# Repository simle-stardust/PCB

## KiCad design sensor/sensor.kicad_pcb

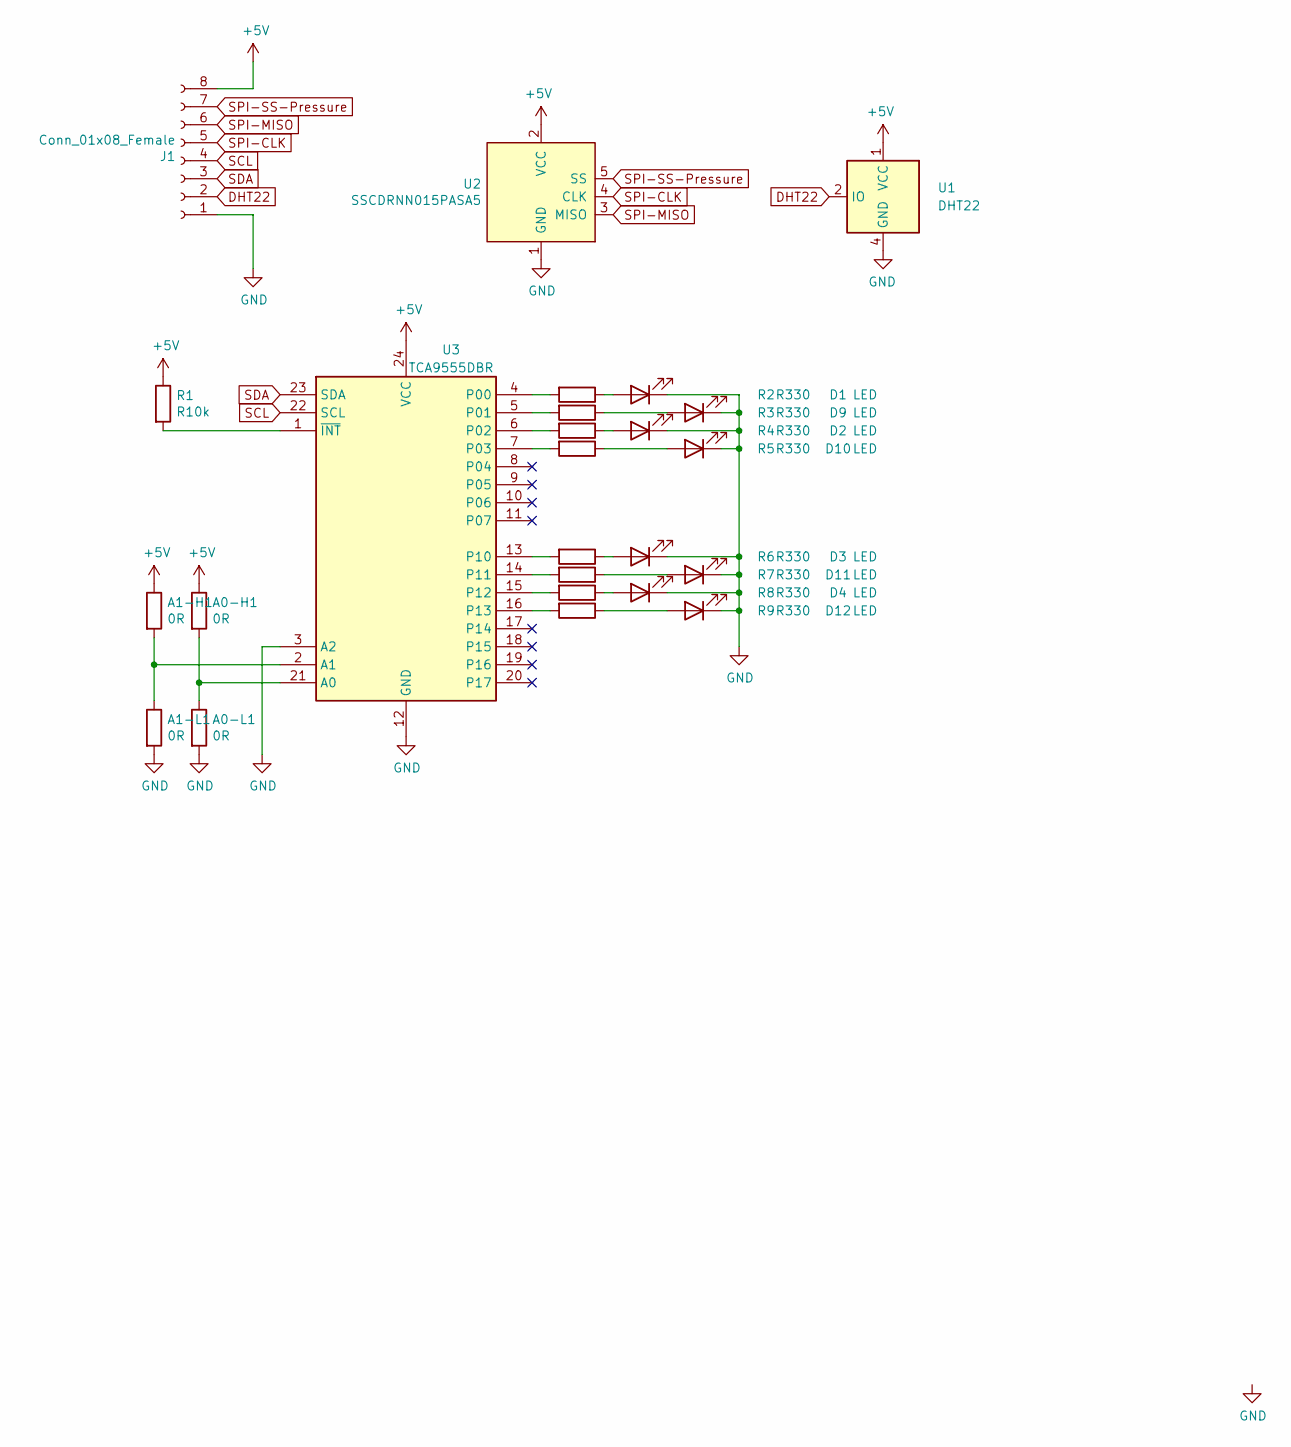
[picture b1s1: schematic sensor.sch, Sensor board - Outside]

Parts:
A0-H1, A0-L1, A1-H1, A1-L1: 0R; R_0603_1608Metric_Pad0.98x0.95mm_HandSolder
D1, D2, D3, D4, D9, D10, D11, D12: LED; LED_D5.0mm
J1: Conn_01x08_Female; 691382040008
R1: R10k; R_0603_1608Metric_Pad0.98x0.95mm_HandSolder
R2, R3, R4, R5, R6, R7, R8, R9: R330; R_0603_1608Metric
U1: DHT22; DHT22_15.0x25.0_P2.54mm_Horizontal
U2: SSCDRNN015PASA5; DIP-8_W8.89mm_SMDSocket_LongPads
U3: TCA9555DBR; SSOP-24_5.3x8.2mm_P0.65mm

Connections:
+5V: A0-H1.1, A1-H1.1, J1.8, R1.1, U1.1 (VCC), U2.2 (VCC), U3.24 (VCC)
DHT22: J1.2, U1.2 (IO)
GND: A0-L1.2, A1-L1.2, D1.1 (K), D2.1 (K), D3.1 (K), D4.1 (K), D9.1 (K), D10.1 (K), D11.1 (K), D12.1 (K), J1.1, U1.4 (GND), U2.1 (GND), U3.3 (A2), U3.12 (GND)
unnamed: A0-H1.2, A0-L1.1, U3.21 (A0)
unnamed: A1-H1.2, A1-L1.1, U3.2 (A1)
unnamed: D1.2 (A), R2.1
unnamed: D2.2 (A), R4.1
unnamed: D3.2 (A), R6.1
unnamed: D4.2 (A), R8.1
unnamed: D9.2 (A), R3.1
unnamed: D10.2 (A), R5.1
unnamed: D11.2 (A), R7.1
unnamed: D12.2 (A), R9.1
unnamed: R1.2, U3.1 (~INT)
unnamed: R2.2, U3.4 (P00)
unnamed: R3.2, U3.5 (P01)
unnamed: R4.2, U3.6 (P02)
unnamed: R5.2, U3.7 (P03)
unnamed: R6.2, U3.13 (P10)
unnamed: R7.2, U3.14 (P11)
unnamed: R8.2, U3.15 (P12)
unnamed: R9.2, U3.16 (P13)
SCL: J1.4, U3.22 (SCL)
SDA: J1.3, U3.23 (SDA)
SPI-CLK: J1.5, U2.4 (CLK)
SPI-MISO: J1.6, U2.3 (MISO)
SPI-SS-Pressure: J1.7, U2.5 (SS)

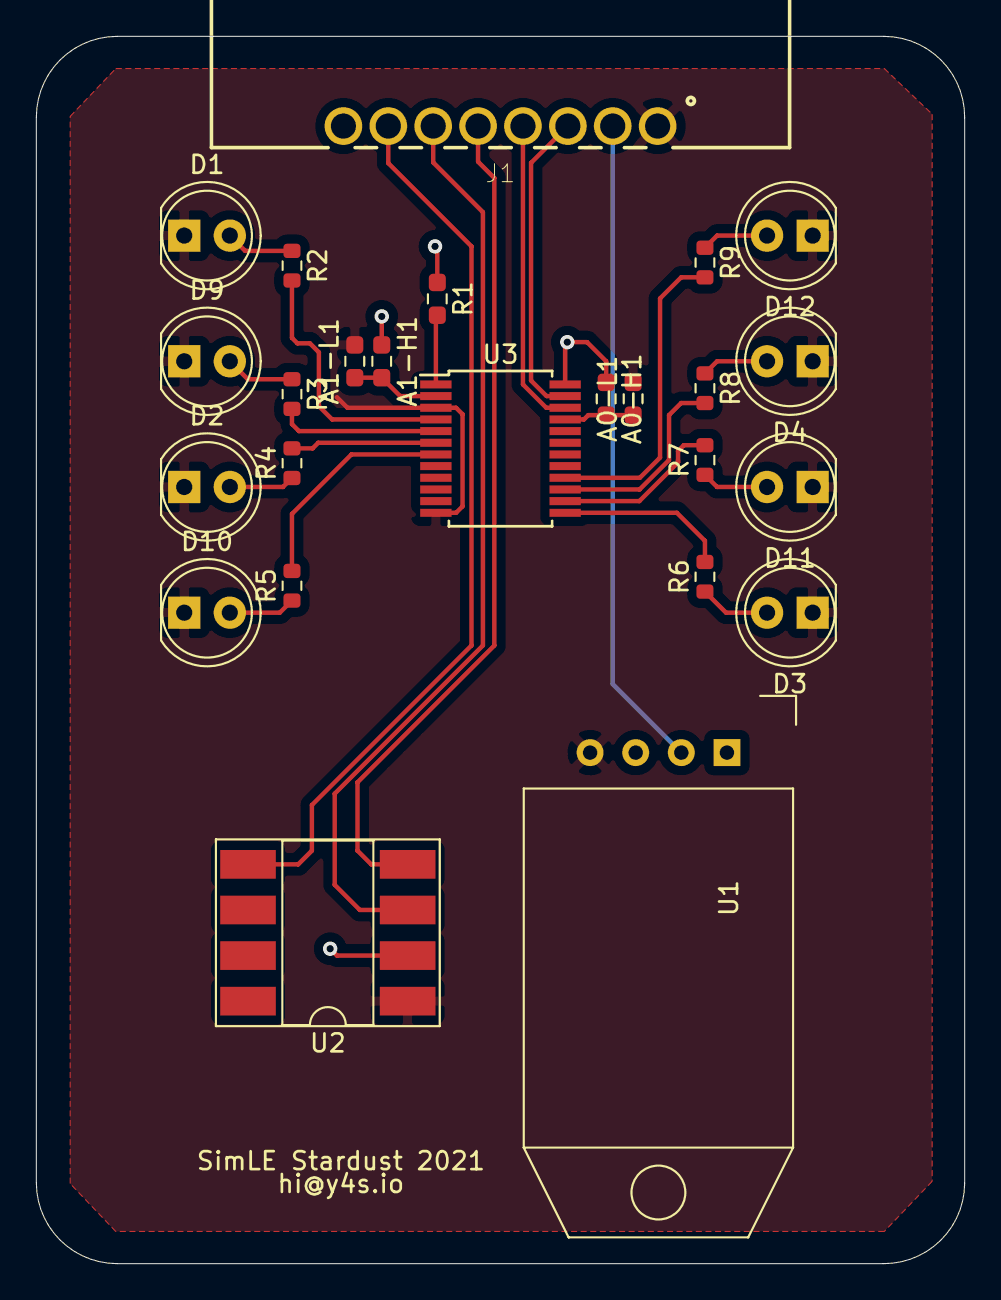
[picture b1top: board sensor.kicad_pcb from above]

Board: 2 copper layers, 51.7 x 68.4 mm, 25 parts (0 on the bottom side), 27 nets.

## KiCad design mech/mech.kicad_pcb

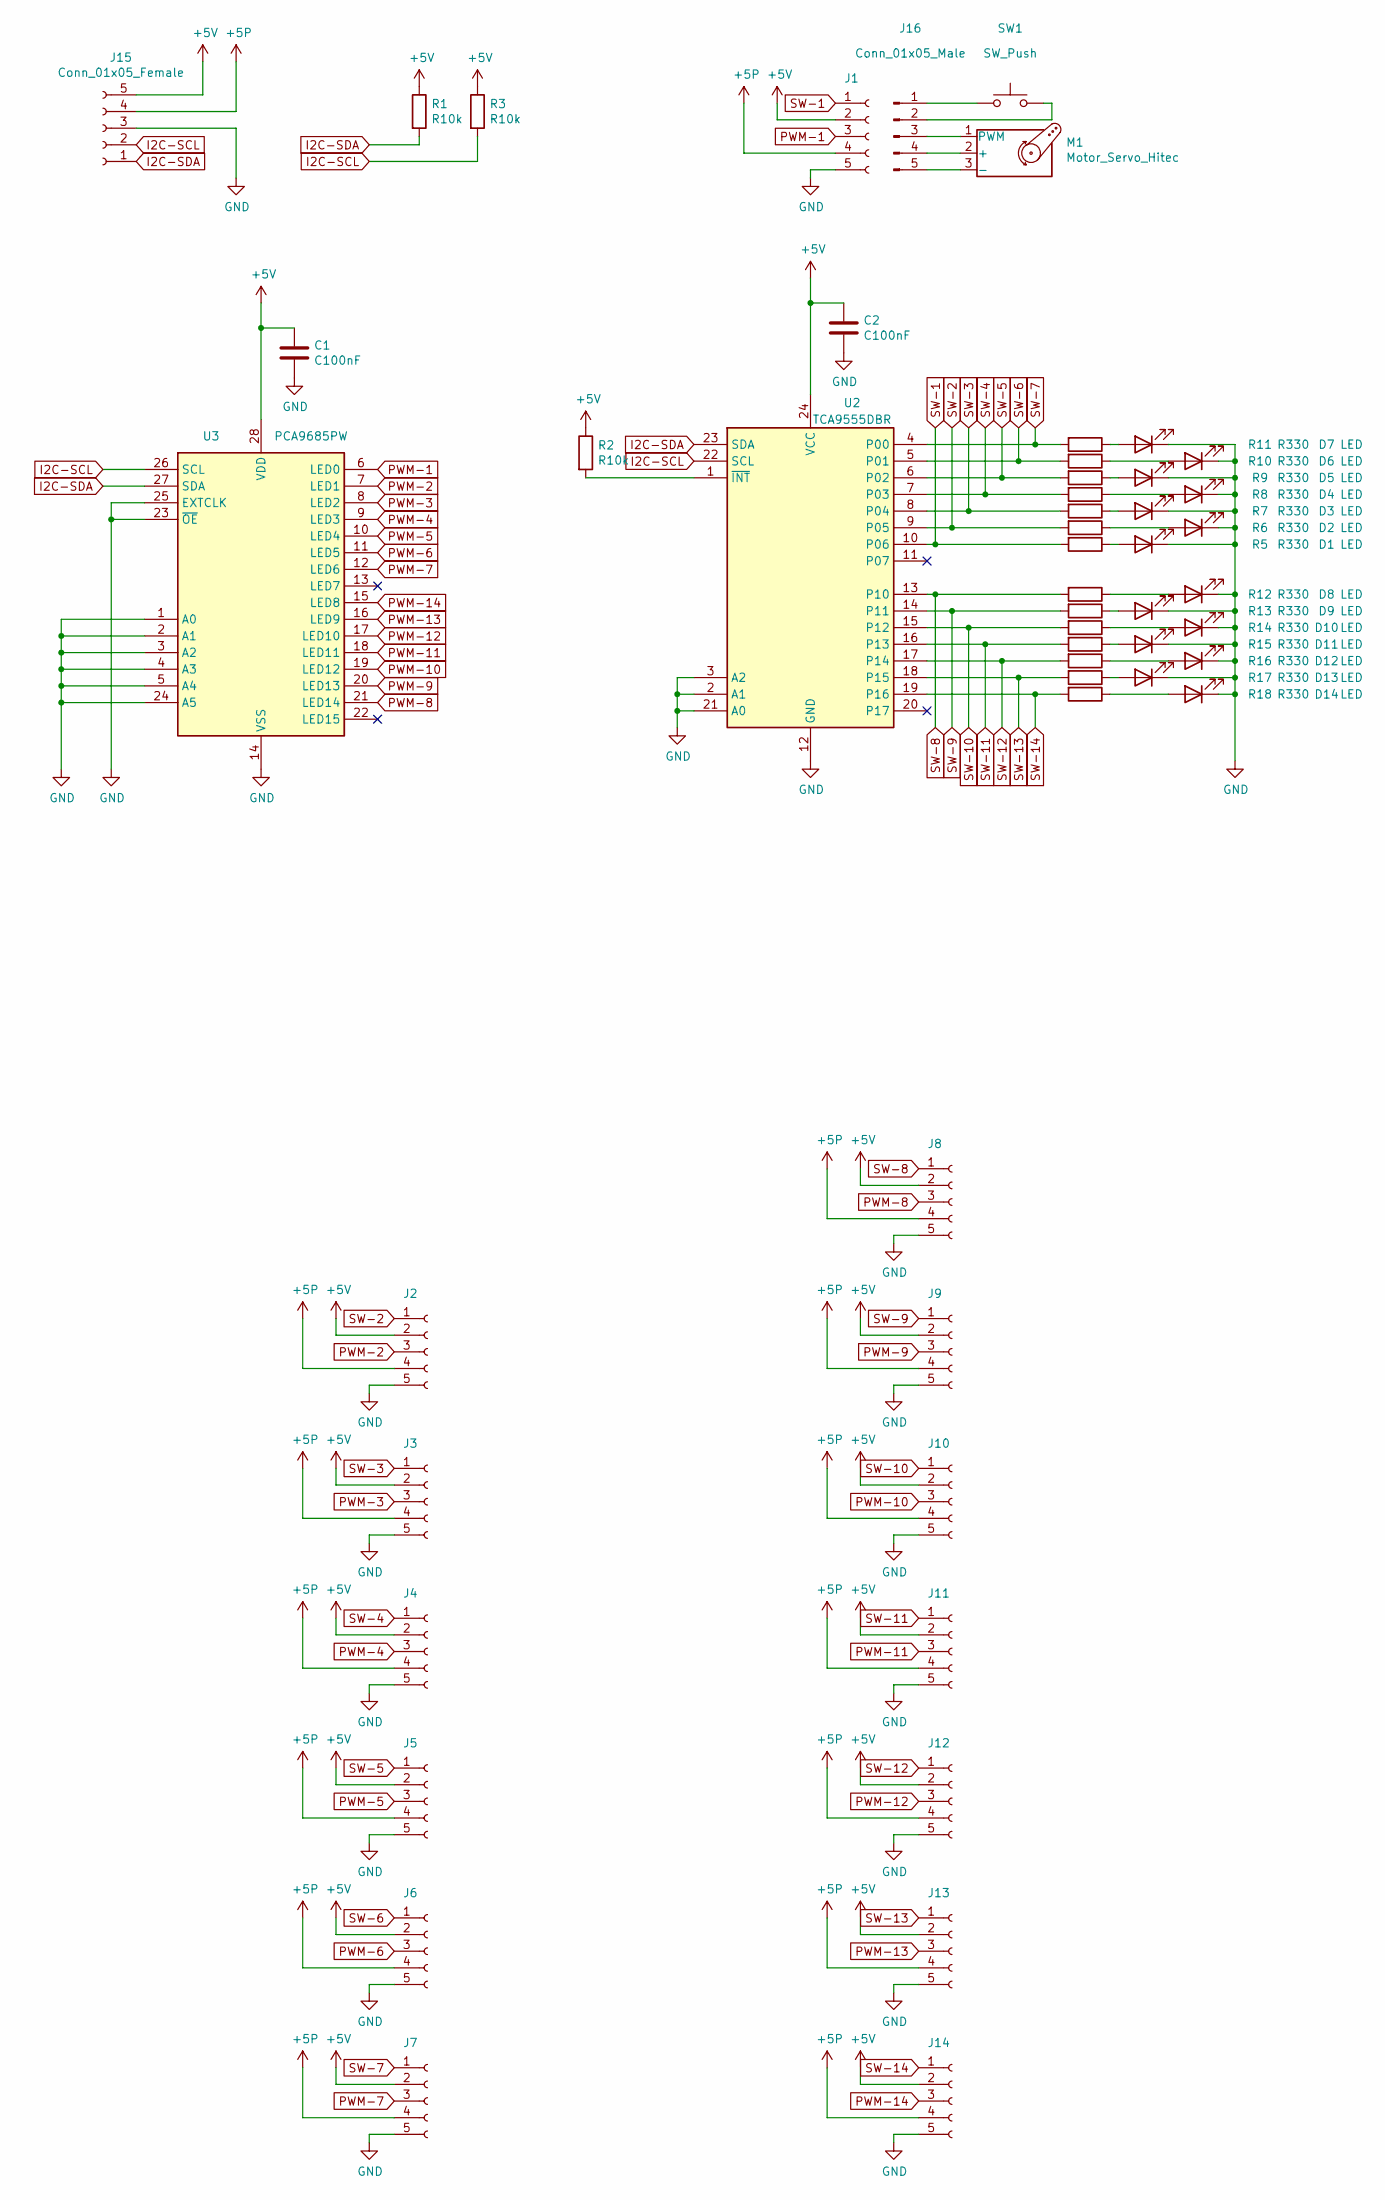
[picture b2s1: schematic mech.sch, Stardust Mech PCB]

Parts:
C1, C2: C100nF; R_0603_1608Metric_Pad0.98x0.95mm_HandSolder
D1, D2, D3, D4, D5, D6, D7, D8, D9, D10, D11, D12, D13, D14: LED; LED_0805_2012Metric_Pad1.15x1.40mm_HandSolder
J1, J2, J3, J4, J5, J6, J7, J8, J9, J10, J11, J12, J13, J14: Conn_01x05_Female; 691382000005
J15: Conn_01x05_Female; 691382030005
J16: Conn_01x05_Male
M1: Motor_Servo_Hitec
R1, R2, R3: R10k; R_0603_1608Metric_Pad0.98x0.95mm_HandSolder
R5, R6, R7, R8, R9, R10, R11, R12, R13, R14, R15, R16, R17, R18: R330; R_0603_1608Metric
SW1: SW_Push
U2: TCA9555DBR; SSOP-24_5.3x8.2mm_P0.65mm
U3: PCA9685PW; TSSOP-28_4.4x9.7mm_P0.65mm

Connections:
+5P: J1.4, J2.4, J3.4, J4.4, J5.4, J6.4, J7.4, J8.4, J9.4, J10.4, J11.4, J12.4, J13.4, J14.4, J15.4
+5V: C1.1, C2.1, J1.2, J2.2, J3.2, J4.2, J5.2, J6.2, J7.2, J8.2, J9.2, J10.2, J11.2, J12.2, J13.2, J14.2, J15.5, R1.1, R2.1, R3.1, U2.24 (VCC), U3.28 (VDD)
GND: C1.2, C2.2, D1.1 (K), D2.1 (K), D3.1 (K), D4.1 (K), D5.1 (K), D6.1 (K), D7.1 (K), D8.1 (K), D9.1 (K), D10.1 (K), D11.1 (K), D12.1 (K), D13.1 (K), D14.1 (K), J1.5, J2.5, J3.5, J4.5, J5.5, J6.5, J7.5, J8.5, J9.5, J10.5, J11.5, J12.5, J13.5, J14.5, J15.3, U2.2 (A1), U2.3 (A2), U2.12 (GND), U2.21 (A0), U3.1 (A0), U3.2 (A1), U3.3 (A2), U3.4 (A3), U3.5 (A4), U3.14 (VSS), U3.23 (~OE), U3.24 (A5), U3.25 (EXTCLK)
I2C-SCL: J15.2, R3.2, U2.22 (SCL), U3.26 (SCL)
I2C-SDA: J15.1, R1.2, U2.23 (SDA), U3.27 (SDA)
unnamed: D1.2 (A), R5.1
unnamed: D2.2 (A), R6.1
unnamed: D3.2 (A), R7.1
unnamed: D4.2 (A), R8.1
unnamed: D5.2 (A), R9.1
unnamed: D6.2 (A), R10.1
unnamed: D7.2 (A), R11.1
unnamed: D8.2 (A), R12.1
unnamed: D9.2 (A), R13.1
unnamed: D10.2 (A), R14.1
unnamed: D11.2 (A), R15.1
unnamed: D12.2 (A), R16.1
unnamed: D13.2 (A), R17.1
unnamed: D14.2 (A), R18.1
unnamed: J16.1, SW1.1
unnamed: J16.2, SW1.2
unnamed: J16.3, M1.1 (PWM)
unnamed: J16.4, M1.2 (+)
unnamed: J16.5, M1.3 (-)
unnamed: R2.2, U2.1 (~INT)
PWM-1: J1.3, U3.6 (LED0)
PWM-2: J2.3, U3.7 (LED1)
PWM-3: J3.3, U3.8 (LED2)
PWM-4: J4.3, U3.9 (LED3)
PWM-5: J5.3, U3.10 (LED4)
PWM-6: J6.3, U3.11 (LED5)
PWM-7: J7.3, U3.12 (LED6)
PWM-8: J8.3, U3.21 (LED14)
PWM-9: J9.3, U3.20 (LED13)
PWM-10: J10.3, U3.19 (LED12)
PWM-11: J11.3, U3.18 (LED11)
PWM-12: J12.3, U3.17 (LED10)
PWM-13: J13.3, U3.16 (LED9)
PWM-14: J14.3, U3.15 (LED8)
SW-1: J1.1, R5.2, U2.10 (P06)
SW-2: J2.1, R6.2, U2.9 (P05)
SW-3: J3.1, R7.2, U2.8 (P04)
SW-4: J4.1, R8.2, U2.7 (P03)
SW-5: J5.1, R9.2, U2.6 (P02)
SW-6: J6.1, R10.2, U2.5 (P01)
SW-7: J7.1, R11.2, U2.4 (P00)
SW-8: J8.1, R12.2, U2.13 (P10)
SW-9: J9.1, R13.2, U2.14 (P11)
SW-10: J10.1, R14.2, U2.15 (P12)
SW-11: J11.1, R15.2, U2.16 (P13)
SW-12: J12.1, R16.2, U2.17 (P14)
SW-13: J13.1, R17.2, U2.18 (P15)
SW-14: J14.1, R18.2, U2.19 (P16)

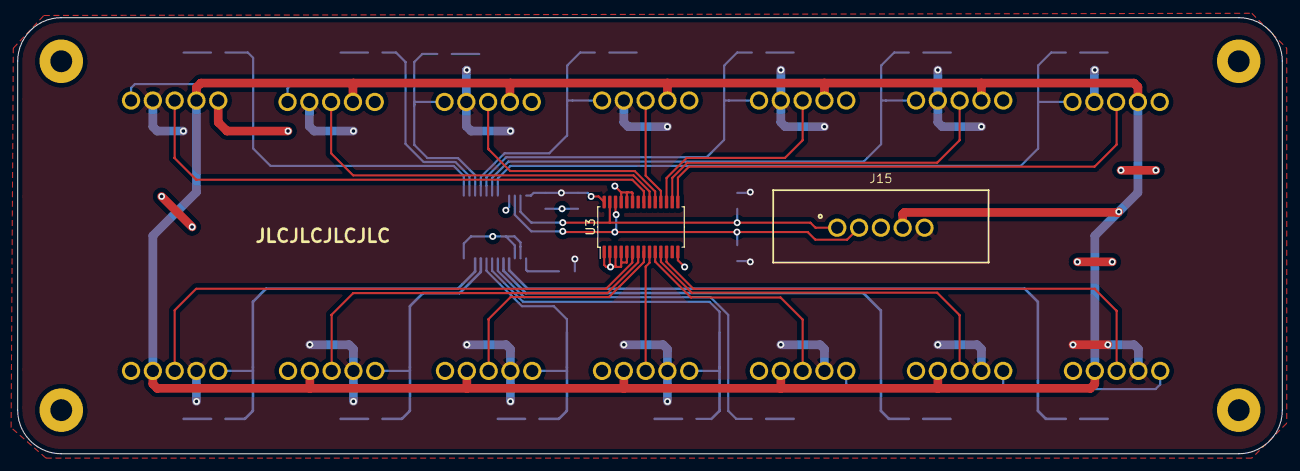
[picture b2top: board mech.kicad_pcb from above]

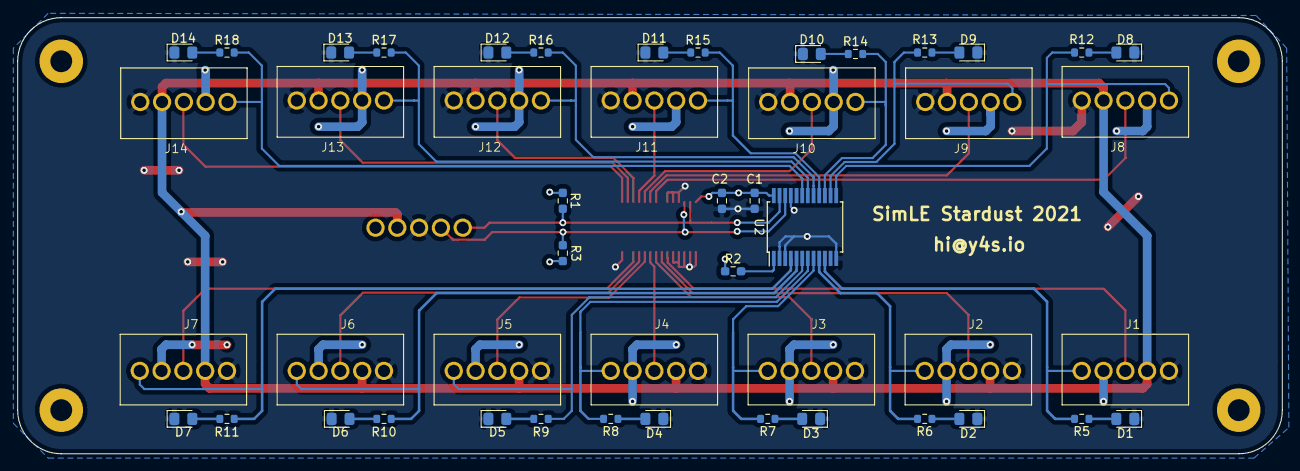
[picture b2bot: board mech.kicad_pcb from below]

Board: 2 copper layers, 145.0 x 50.0 mm, 50 parts (48 on the bottom side), 48 nets.

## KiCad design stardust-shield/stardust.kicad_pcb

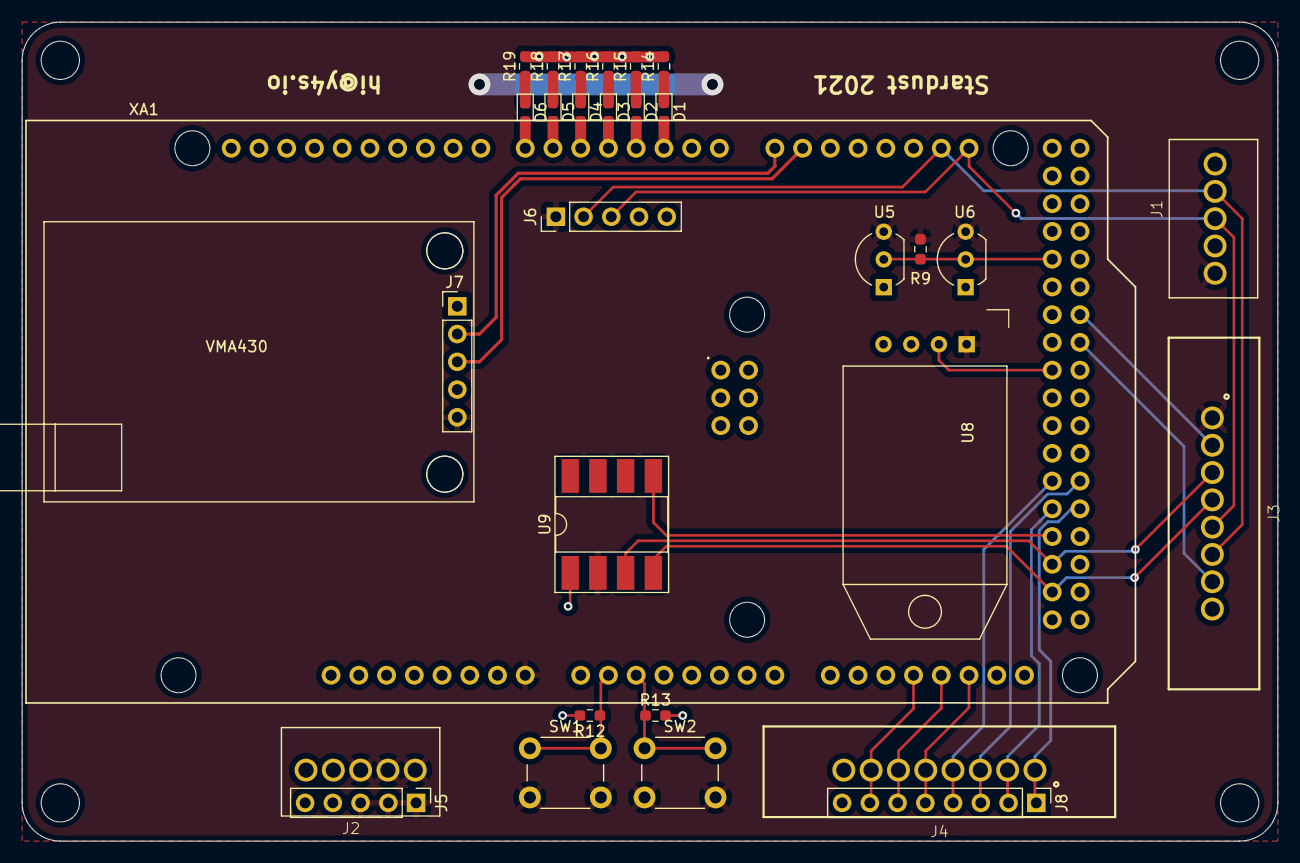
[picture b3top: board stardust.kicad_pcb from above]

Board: 2 copper layers, 115.0 x 75.0 mm, 30 parts (0 on the bottom side), 34 nets.

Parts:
D1, D2, D3, D4, D5, D6: LED; LED_0603_1608Metric_Pad1.05x0.95mm_HandSolder
J1: Experiment PCB; 691382000005
J2: Power PCB; 691382000005
J3: Sensor PCB; 691382030008
J4: Power PCB; 691382030008
J5: Power PCB Goldpin; PinHeader_1x05_P2.54mm_Vertical
J6: DS3231M; PinHeader_1x05_P2.54mm_Vertical
J7: VMA430; PinHeader_1x05_P2.54mm_Vertical
J8: Power PCB Goldpin; PinHeader_1x08_P2.54mm_Vertical
R9: 4.7k; R_0603_1608Metric_Pad0.98x0.95mm_HandSolder
R12, R13: 10k; R_0603_1608Metric_Pad0.98x0.95mm_HandSolder
R14, R15, R16, R17, R18, R19: 1k; R_0603_1608Metric_Pad0.98x0.95mm_HandSolder
SW1, SW2: SW_Push; SW_PUSH_6mm
U5, U6: DS18B20; TO-92_Inline_Wide
U8: DHT22; DHT22_15.0x25.0_P2.54mm_Horizontal
U9: SSCDRNN015PASA5; DIP-8_W8.89mm_SMDSocket_LongPads
XA1: Arduino_Mega2560_Shield

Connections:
1Wire: R9.2, U5.2, U6.2, XA1.D28
+5V: J1.1, J2.1, J2.2, J2.3, J3.1, J5.1, J5.2, J5.3, J6.1, J7.5, R9.1, SW1.2, SW2.2, U5.3, U6.3, U8.1, U9.2, XA1.VIN
Button-1: R12.1, SW1.1, XA1.A1
Button-2: R13.1, SW2.1, XA1.A2
DHT22-2: J3.7, XA1.D35
DHT22-3: U8.2, XA1.D36
GND: J1.5, J2.4, J2.5, J3.8, J4.8, J5.4, J5.5, J6.5, J7.4, J8.8, R12.2, R13.2, R14.2, R15.2, R16.2, R17.2, R18.2, R19.2, U5.1, U6.1, U8.4, U9.1, XA1.GND1, XA1.GND2, XA1.GND3, XA1.GND5, XA1.GND6
Heating-PWM: J4.2, J8.2, XA1.D46
I2C-SCL: J1.3, J3.5, J6.3, XA1.D21
I2C-SDA: J1.4, J3.6, J6.2, XA1.D20
INA1: J4.5, J8.5, XA1.A13
INA2: J4.6, J8.6, XA1.A12
INA3: J4.7, J8.7, XA1.A11
LED-1: D1.2, XA1.D2
LED-2: D2.2, XA1.D3
LED-3: D3.2, XA1.D4
LED-4: D4.2, XA1.D5
LED-5: D5.2, XA1.D6
LED-6: D6.2, XA1.D7
unnamed: D1.1, R14.1
unnamed: D2.1, R15.1
unnamed: D3.1, R16.1
unnamed: D4.1, R17.1
unnamed: D5.1, R18.1
unnamed: D6.1, R19.1
Pump-1-PWM: J4.3, J8.3, XA1.D45
Pump-2-PWM: J4.4, J8.4, XA1.D44
RX3: J7.3, XA1.D15
SPI-CLK: J3.4, U9.4, XA1.D52
SPI-MISO: J3.3, U9.3, XA1.D50
SPI-SS-Pressure-1: J3.2, XA1.D33
SPI-SS-Pressure-2: U9.5, XA1.D48
Servo-GPIO: J4.1, J8.1, XA1.D47
TX3: J7.2, XA1.D14

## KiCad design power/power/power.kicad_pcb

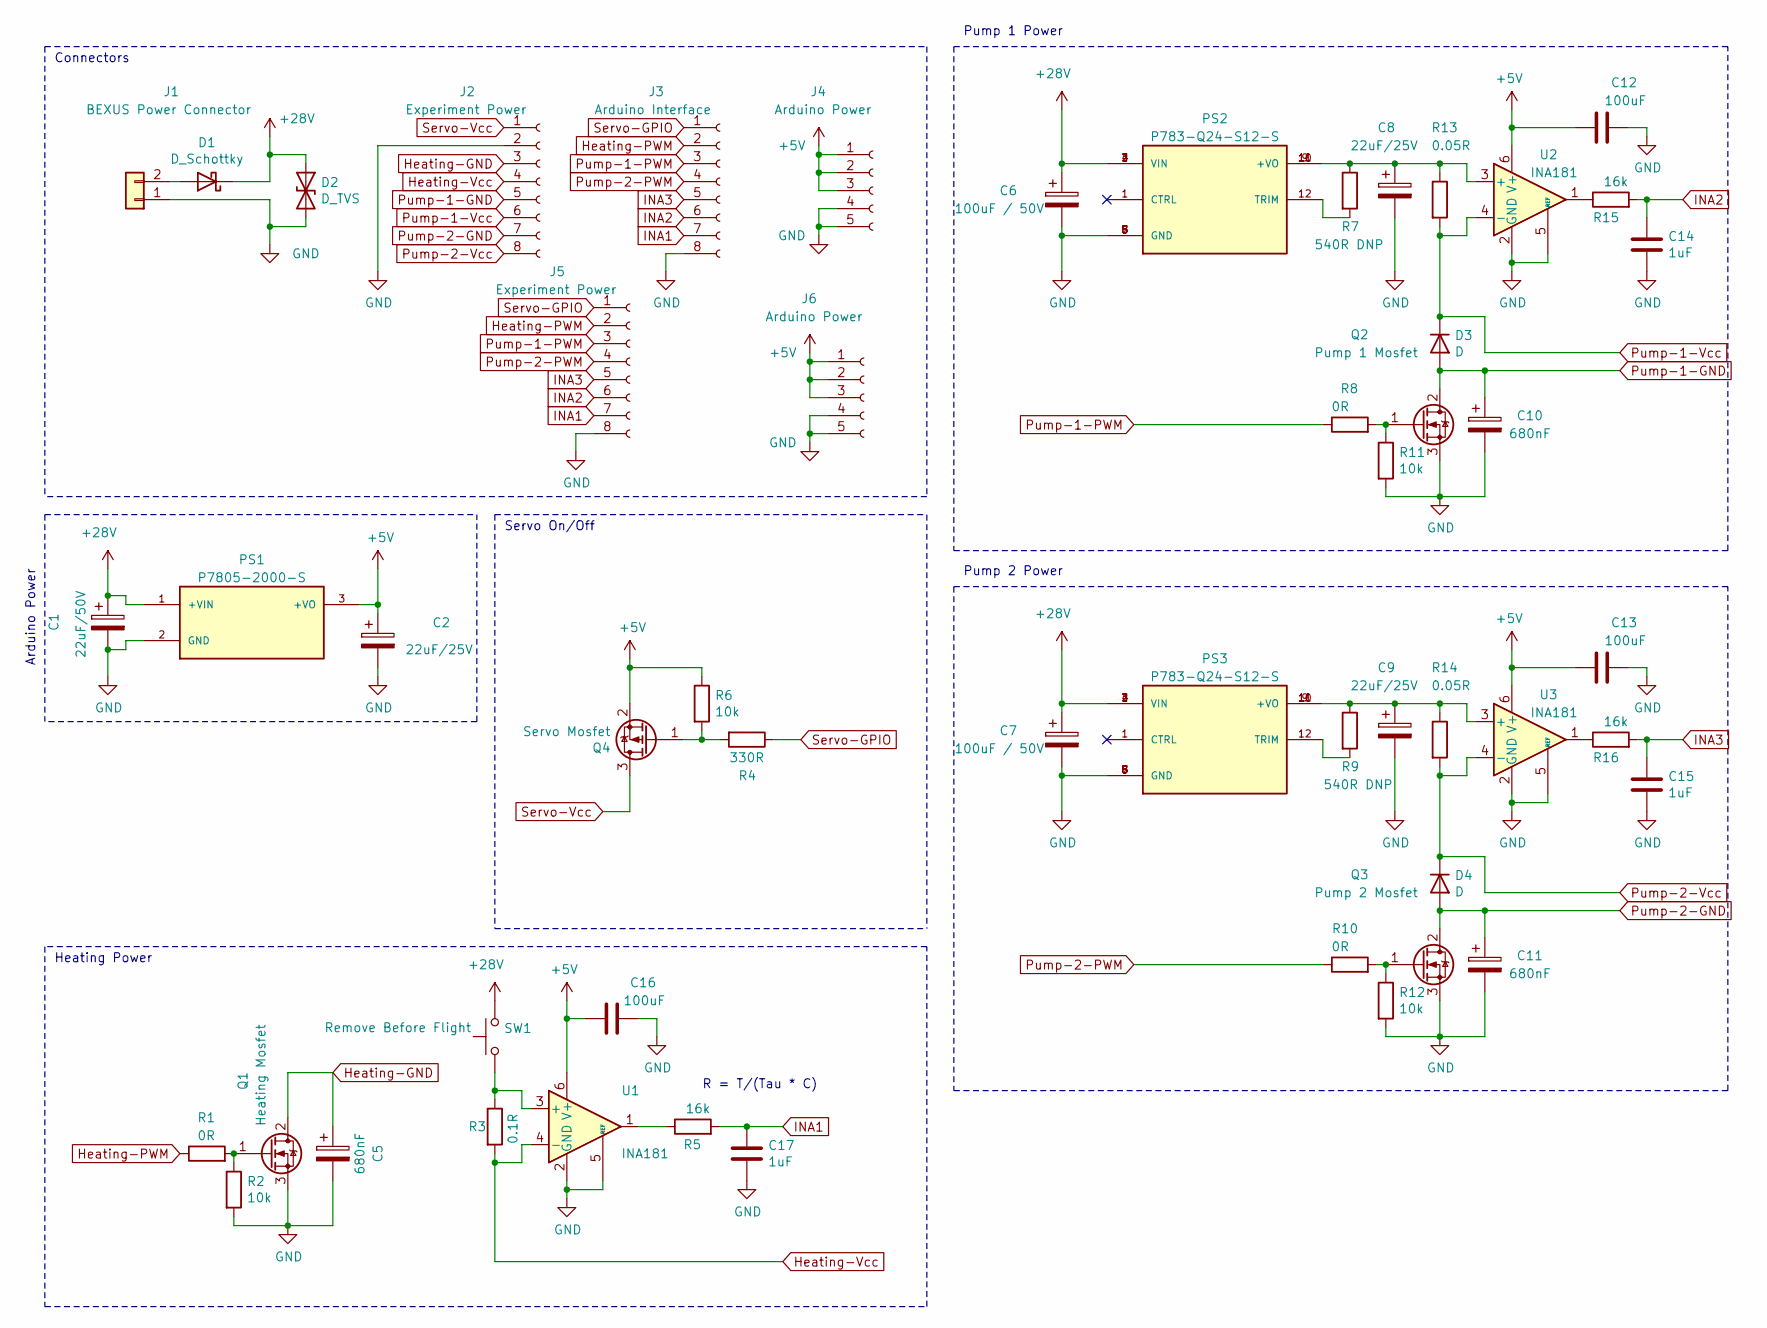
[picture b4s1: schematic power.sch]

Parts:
C1: 22uF/50V; CP_Radial_D5.0mm_P2.50mm
C2, C8, C9: 22uF/25V; CP_Radial_D5.0mm_P2.50mm
C5, C10, C11: 680nF; CP_Radial_D5.0mm_P2.50mm
C6, C7: 100uF / 50V; CP_Radial_D5.0mm_P2.50mm
C12, C13, C16: 100uF; C_0603_1608Metric_Pad1.08x0.95mm_HandSolder
C14, C15, C17: 1uF; C_0603_1608Metric_Pad1.08x0.95mm_HandSolder
D1: D_Schottky; D_SMA
D2: D_TVS; D_SMB_Handsoldering
D3, D4: D; D_DO-15_P12.70mm_Horizontal
J1: BEXUS Power Connector; SolderWire-0.5sqmm_1x02_P4.6mm_D0.9mm_OD2.1mm_Relief
J2: Experiment Power; 691382030008
J3: Arduino Interface; 691382030008
J4: Arduino Power; 691382000005
J5: Experiment Power; PinHeader_1x08_P2.54mm_Vertical
J6: Arduino Power; PinHeader_1x05_P2.54mm_Vertical
PS1: P7805-2000-S; CONV_P7805-2000-S; PARTREV 1.01
PS2, PS3: P783-Q24-S12-S; CONV_P783-Q24-S12-S; PARTREV 1.0
Q1: Heating Mosfet; TO-126-3_Horizontal_TabDown
Q2: Pump 1 Mosfet; TO-126-3_Horizontal_TabDown
Q3: Pump 2 Mosfet; TO-126-3_Horizontal_TabDown
Q4: Servo Mosfet; TSOT-23
R1, R8, R10: 0R; R_0603_1608Metric_Pad0.98x0.95mm_HandSolder
R2, R6, R11, R12: 10k; R_0603_1608Metric_Pad0.98x0.95mm_HandSolder
R3: 0.1R; R_0603_1608Metric_Pad0.98x0.95mm_HandSolder
R4: 330R; R_0603_1608Metric_Pad0.98x0.95mm_HandSolder
R5, R15, R16: 16k; R_0603_1608Metric_Pad0.98x0.95mm_HandSolder
R7, R9: 540R DNP; R_0603_1608Metric_Pad0.98x0.95mm_HandSolder
R13, R14: 0.05R; R_0603_1608Metric_Pad0.98x0.95mm_HandSolder
SW1: Remove Before Flight; PinHeader_1x02_P2.54mm_Vertical
U1, U2, U3: INA181; SOT-23-6

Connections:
+5V: C2.1, C12.1, C13.1, C16.1, J4.1, J4.2, J4.3, J6.1, J6.2, J6.3, PS1.3 (+VO), Q4.2 (S), R6.1, U1.6 (V+), U2.6 (V+), U3.6 (V+)
+28V: C1.1, C6.1, C7.1, D1.1 (K), D2.1 (A1), PS1.1 (+VIN), PS2.2 (VIN), PS2.3 (VIN), PS2.4 (VIN), PS3.2 (VIN), PS3.3 (VIN), PS3.4 (VIN), SW1.2
GND: C1.2, C2.2, C5.2, C6.2, C7.2, C8.2, C9.2, C10.2, C11.2, C12.2, C13.2, C14.2, C15.2, C16.2, C17.2, D2.2 (A2), J1.1, J2.2, J3.8, J4.4, J4.5, J5.8, J6.4, J6.5, PS1.2 (GND), PS2.5 (GND), PS2.6 (GND), PS2.7 (GND), PS2.8 (GND), PS3.5 (GND), PS3.6 (GND), PS3.7 (GND), PS3.8 (GND), Q1.3 (S), Q2.3 (S), Q3.3 (S), R2.2, R11.2, R12.2, U1.2 (GND), U1.5 (REF), U2.2 (GND), U2.5 (REF), U3.2 (GND), U3.5 (REF)
Heating-GND: C5.1, J2.3, Q1.2 (D)
Heating-PWM: J3.2, J5.2, R1.1
Heating-Vcc: J2.4, R3.2, U1.4 (-)
INA1: C17.1, J3.7, J5.7, R5.2
INA2: C14.1, J3.6, J5.6, R15.2
INA3: C15.1, J3.5, J5.5, R16.2
unnamed: C8.1, PS2.9 (+VO), PS2.10 (+VO), PS2.11 (+VO), R7.1, R13.1, U2.3 (+)
unnamed: C9.1, PS3.9 (+VO), PS3.10 (+VO), PS3.11 (+VO), R9.1, R14.1, U3.3 (+)
unnamed: D1.2 (A), J1.2
unnamed: PS2.12 (TRIM), R7.2
unnamed: PS3.12 (TRIM), R9.2
unnamed: Q1.1 (G), R1.2, R2.1
unnamed: Q2.1 (G), R8.2, R11.1
unnamed: Q3.1 (G), R10.2, R12.1
unnamed: Q4.1 (G), R4.2, R6.2
unnamed: R3.1, SW1.1, U1.3 (+)
unnamed: R5.1, U1.1
unnamed: R15.1, U2.1
unnamed: R16.1, U3.1
Pump-1-GND: C10.1, D3.2 (A), J2.5, Q2.2 (D)
Pump-1-PWM: J3.3, J5.3, R8.1
Pump-1-Vcc: D3.1 (K), J2.6, R13.2, U2.4 (-)
Pump-2-GND: C11.1, D4.2 (A), J2.7, Q3.2 (D)
Pump-2-PWM: J3.4, J5.4, R10.1
Pump-2-Vcc: D4.1 (K), J2.8, R14.2, U3.4 (-)
Servo-GPIO: J3.1, J5.1, R4.1
Servo-Vcc: J2.1, Q4.3 (D)

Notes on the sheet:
Servo On/Off
Arduino Power
Connectors
R = T/(Tau * C)
Heating Power
Pump 1 Power
Pump 2 Power

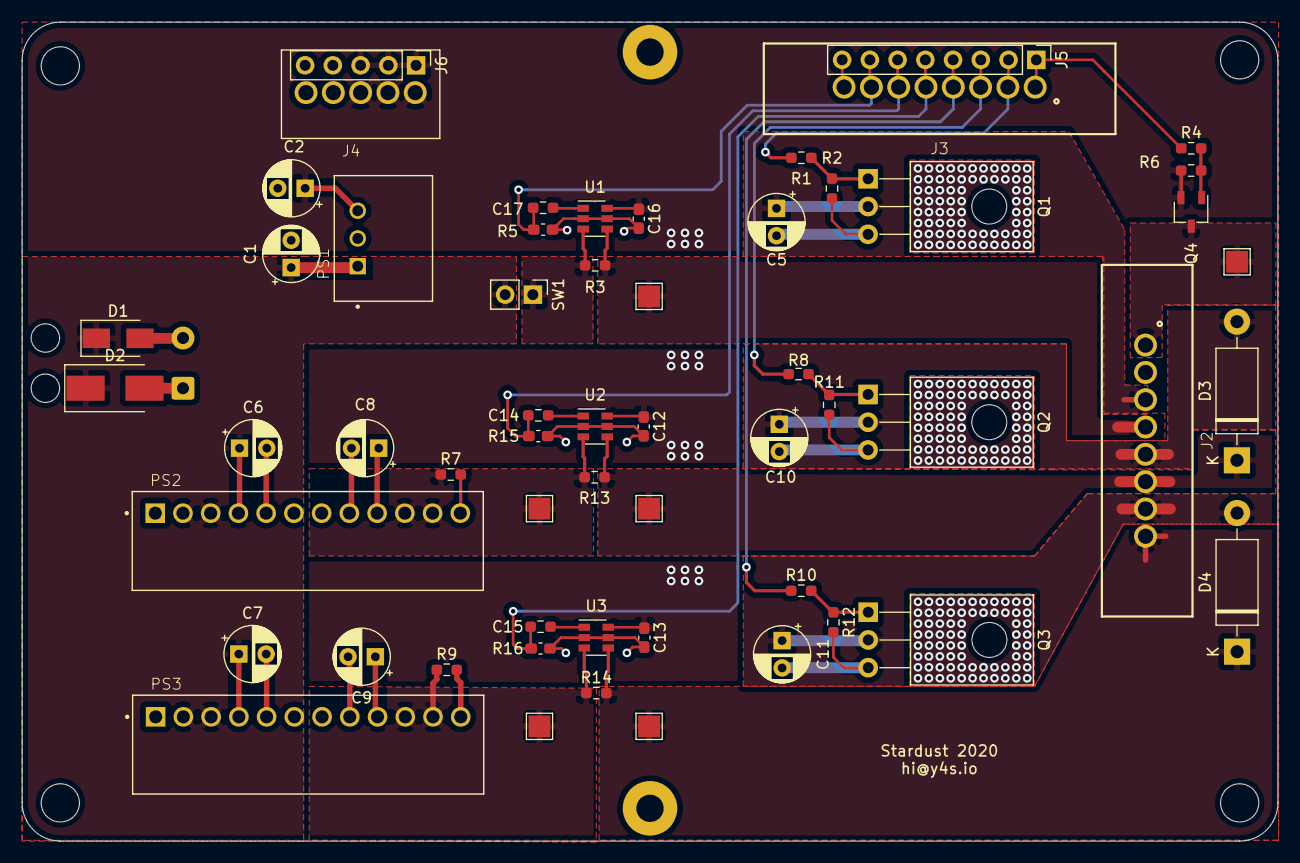
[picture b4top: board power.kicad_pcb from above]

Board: 2 copper layers, 115.0 x 75.0 mm, 52 parts (1 on the bottom side), 30 nets.

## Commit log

2020-04-18 initial git release
2020-04-18 ignore plot files
2020-04-18 fix edge corner
2020-04-18 add JLC part number stub
2020-04-19 ADC + PCA9685 version
2020-04-19 mumble
2020-04-19 final
2020-04-22 sensor board init
2020-04-22 modifications
2020-04-22 init
2020-04-22 copy mech
2020-04-22 finish preplacement
2020-04-24 main pcb
2020-04-24 fix border, move mosfet, add labels
2020-04-24 add footprints, clear board
2020-04-24 fix pressure sensor footprint
2020-04-24 add JLC id placeholder
2020-04-25 move mosfet to mech board, controll pump via gnd
2020-04-25 update fill area
2020-04-25 add pump pull-down, clean up paths
2020-04-30 add db9 models, and update footprints
2020-07-26 rev.2 init
2020-08-05 refill
2020-08-10 final 2.0
2020-08-10 tweaks
2020-08-10 add capacitors
2020-08-12 final touches
2020-08-12 mech pcb tweaks
2020-08-12 finalize and cleanup
2021-02-23 WIP sensor PCB
2021-02-24 WIP sensor PCB - delete files
2021-07-05 change everything
